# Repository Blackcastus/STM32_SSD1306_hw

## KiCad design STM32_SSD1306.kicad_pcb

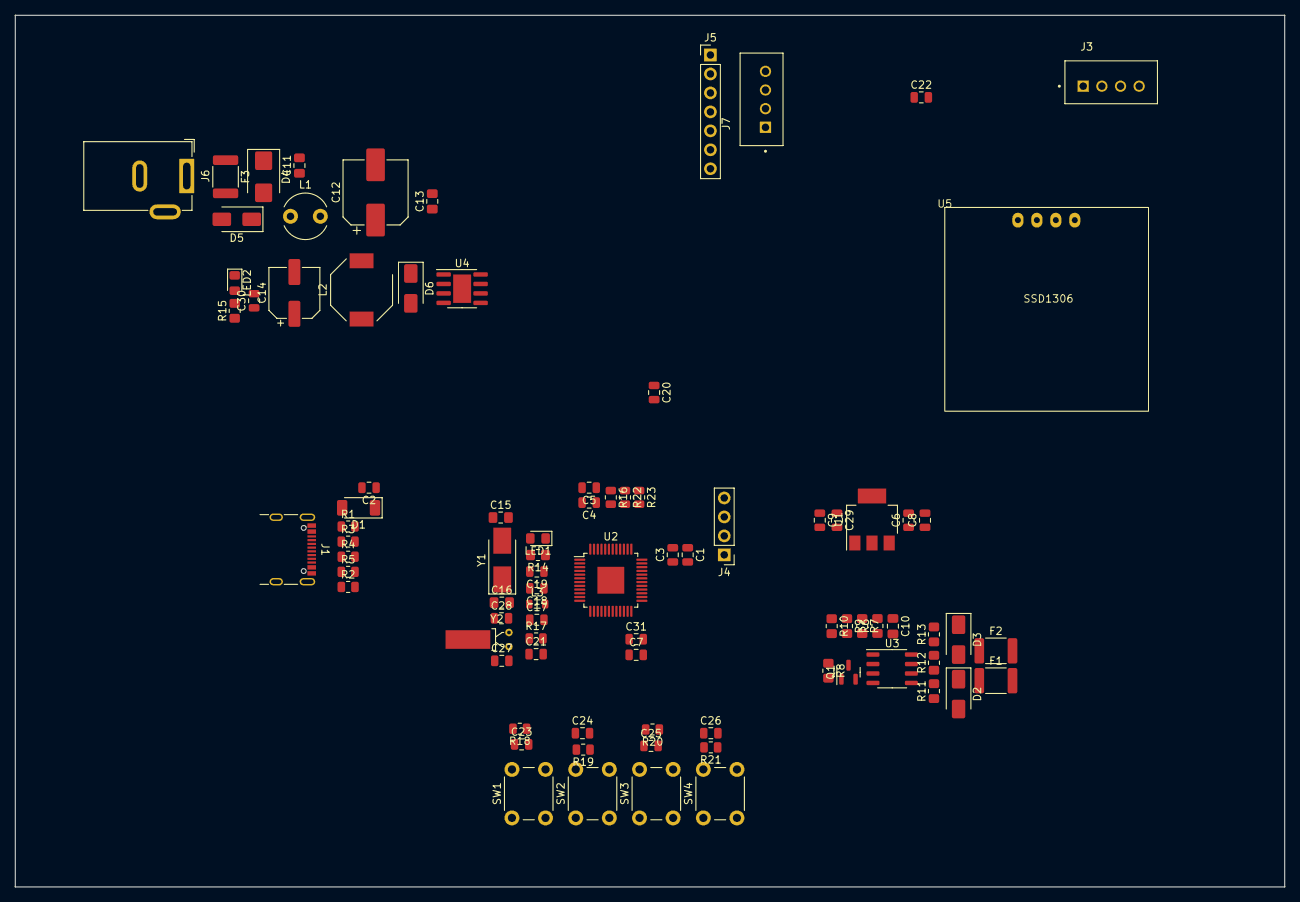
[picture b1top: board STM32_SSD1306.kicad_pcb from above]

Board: 2 copper layers, 170.1 x 116.8 mm, 87 parts (1 on the bottom side), 47 nets, no tracks yet.

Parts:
BT1: Battery_Cell; CR1220
C1, C6, C29: 10uF; C_0805_2012Metric
C2, C3, C4, C5, C7, C8, C9, C17, C19, C20, C21, C22, C23, C24, C25, C26, C30, C31: 100nF; C_0805_2012Metric
C10, C13: 100nF; C_0805_2012Metric_Pad1.18x1.45mm_HandSolder
C11: 1uF_50V; C_0805_2012Metric_Pad1.18x1.45mm_HandSolder
C12: 220uF_50V; CP_Elec_8x10.5
C14: 180uF_35v; CP_Elec_6.3x9.9
C15, C16: 20pF; C_0805_2012Metric_Pad1.18x1.45mm_HandSolder
C18: 1uF; C_0805_2012Metric
C27, C28: 10pF; C_0805_2012Metric
D1: SS2x_SMA; D_SOD-128
D2, D3: D_TVS; D_SMA
D4: TVS; D_SMB
D5: 1N4007_M7; D_SMA
D6: 1N5820; D_SMA
F1, F2: Fuse; Fuse_1812_4532Metric_Pad1.30x3.40mm_HandSolder
F3: Polyfuse; Fuse_1812_4532Metric_Pad1.30x3.40mm_HandSolder
J1: USB_C_Receptacle_USB2.0; USB_C_Receptacle_GCT_USB4105-xx-A_16P_TopMnt_Horizontal
J3, J7: Header_4P_2.54mm
J4: Conn_01x04; PinHeader_1x04_P2.54mm_Vertical
J5: Conn_01x07_Pin; PinHeader_1x07_P2.54mm_Vertical
J6: Jack-DC; BarrelJack_GCT_DCJ200-10-A_Horizontal
L1: L_Ferrite; L_Radial_D6.0mm_P4.00mm
L2: 68uH_2A; L_Bourns-SRU8028_8.0x8.0mm
L3: L600R; L_0805_2012Metric
LED1, LED2: BLUE; LED_0805_2012Metric_Pad1.15x1.40mm_HandSolder
Q1: 2SC1815-HF; SOT-23
R1, R2: 5.1k; R_0805_2012Metric
R3: 1.5k; R_0805_2012Metric
R4, R5: 22R; R_0805_2012Metric
R6, R9, R10: 10K; R_0805_2012Metric_Pad1.20x1.40mm_HandSolder
R7, R11, R13: 4.7K; R_0805_2012Metric_Pad1.20x1.40mm_HandSolder
R8: 2.2K; R_0805_2012Metric_Pad1.20x1.40mm_HandSolder
R12: 120R; R_0805_2012Metric_Pad1.20x1.40mm_HandSolder
R14, R15: 1K; R_0805_2012Metric_Pad1.20x1.40mm_HandSolder
R16, R17: 10k; R_0805_2012Metric
R18, R19, R20, R21: 10K; R_0805_2012Metric
R22, R23: 4.7K; R_0805_2012Metric
SW1, SW2, SW3, SW4: SW_Push; SW_PUSH_6mm_H7.3mm
U1: ASM1117-3V3; SOT-223
U2: STM32F103C8Tx; LQFP-48-1EP_7x7mm_P0.5mm_EP3.6x3.6mm
U3: MAX485; SO-8_3.9x4.9mm_P1.27mm
U4: XL1509; SOIC-8-1EP_3.9x4.9mm_P1.27mm_EP2.41x3.81mm
U5: SSD1306
Y1: 8MHz; Crystal_SMD_5032-2Pin_5.0x3.2mm_HandSoldering
Y2: 8MHz; Crystal_DS26_D2.0mm_L6.0mm_Horizontal_1EP_style1

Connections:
+3.3V: C10.2, J5.1, R9.1, R10.1, R11.1, R14.1, R18.1, R19.1, R20.1, R21.1, R22.1, R23.1, U3.8 (VCC)
+3V3: C1.1, C3.2, C4.2, C5.2, C7.2, C9.1, C17.1, C22.2, C29.1, C31.2, J4.2, J7.2, L3.1, R17.1, U1.2 (OUT), U1.4 (OUT), U2.24 (VDD), U2.36 (VDD), U2.48 (VDD), U5.2 (VCC)
+5V: C2.1, C6.1, C8.1, C14.1, C30.1, D1.1 (K), L2.2, R15.1, U1.3 (IN), U4.3 (FB)
+12V: F3.1, J6.1
/+A: F1.2, J3.1
/-B: F2.2, J3.2
/BLINK: LED1.1 (K), U2.2 (PC13)
/BTN_DOWN: C24.1, R19.2, SW2.1, U2.26 (PB13)
/BTN_OK: C26.1, R21.2, SW4.1, U2.28 (PB15)
/BTN_SELECT: C25.1, R20.2, SW3.1, U2.27 (PB14)
/BTN_UP: C23.1, R18.2, SW1.1, U2.25 (PB12)
/I2C1_SCL: J7.3, R23.2, U2.42 (PB6), U5.3 (SCK)
/I2C1_SDA: J7.4, R22.2, U2.43 (PB7), U5.4 (SDA)
/SPI1_CS1: J5.6, U2.18 (PB0)
/SPI1_CS2: J5.7, U2.19 (PB1)
/SPI1_MISO: J5.4, U2.16 (PA6)
/SPI1_MOSI: J5.5, U2.17 (PA7)
/SPI1_SCK: J5.3, U2.15 (PA5)
/SWCLK: J4.4, U2.37 (PA14)
/SWDIO: J4.3, U2.34 (PA13)
/UART0_RXD: R6.2, R7.1, U2.31 (PA10)
/UART0_TXD: R8.1, U2.30 (PA9)
/XTA32IN: C27.2, U2.3 (PC14), Y2.2
/XTA32OUT: C28.2, U2.4 (PC15), Y2.1
/XTALIN: C15.2, U2.5 (PD0), Y1.2
/XTALOUT: C16.2, U2.6 (PD1), Y1.1
GND: BT1.2 (-), C1.2, C2.2, C3.1, C4.1, C5.1, C6.2, C7.1, C8.2, C9.2, C10.1, C11.2, C12.2, C13.2, C14.2, C15.1, C16.1, C17.2, C18.2, C19.2, C20.1, C21.1, C22.1, C23.2, C24.2, C25.2, C26.2, C27.1, C28.1, C29.2, C30.2, C31.1, D2.2 (A2), D3.1 (A1), D4.1 (A1), D6.2 (A), J1.A1 (GND), J1.A12 (GND), J1.B1 (GND), J1.B12 (GND), J1.S1 (SHIELD), J4.1, J5.2, J6.2, J7.1, LED2.1 (K), Q1.2 (E), R1.2, R2.2, R6.1, R13.2, R16.1, SW1.2, SW2.2, SW3.2, SW4.2, U1.1 (GND), U2.8 (VSSA), U2.23 (VSS), U2.35 (VSS), U2.47 (VSS), U3.5 (GND), U4.4 (On/Off), U4.5 (GND), U5.1 (GND)
unnamed: BT1.1 (+), C20.2, U2.1 (VBAT)
unnamed: D1.2 (A), J1.A4 (VBUS), J1.A9 (VBUS), J1.B4 (VBUS), J1.B9 (VBUS)
unnamed: D2.1 (A1), F1.1, R11.2, R12.1, U3.6 (A)
unnamed: D3.2 (A2), F2.1, R12.2, R13.1, U3.7 (B)
unnamed: D4.2 (A2), D5.2 (A), F3.2
unnamed: C11.1, D5.1 (K), L1.1
unnamed: D6.1 (K), L2.1, U4.2 (Vo)
unnamed: J1.A5 (CC1), R1.1
unnamed: J1.B5 (CC2), R2.1
unnamed: J1.A6 (D+), J1.B6 (D+), R3.1, R5.1
unnamed: J1.A7 (D-), J1.B7 (D-), R4.1
unnamed: LED1.2 (A), R14.2
unnamed: LED2.2 (A), R15.2
unnamed: Q1.1 (B), R8.2
unnamed: Q1.3 (C), R10.2, U3.2 (~RE), U3.3 (DE)
unnamed: R16.2, U2.44 (BOOT0)
unnamed: C21.2, R17.2, U2.7 (NRST)
unnamed: C18.1, C19.1, L3.2, U2.9 (VDDA)
unnamed: R7.2, R9.2, U3.1 (RO)
unnamed: C12.1, C13.1, L1.2, U4.1 (Vi)

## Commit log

2023-05-13 Schematic
2023-05-14 Start Layout PCB
